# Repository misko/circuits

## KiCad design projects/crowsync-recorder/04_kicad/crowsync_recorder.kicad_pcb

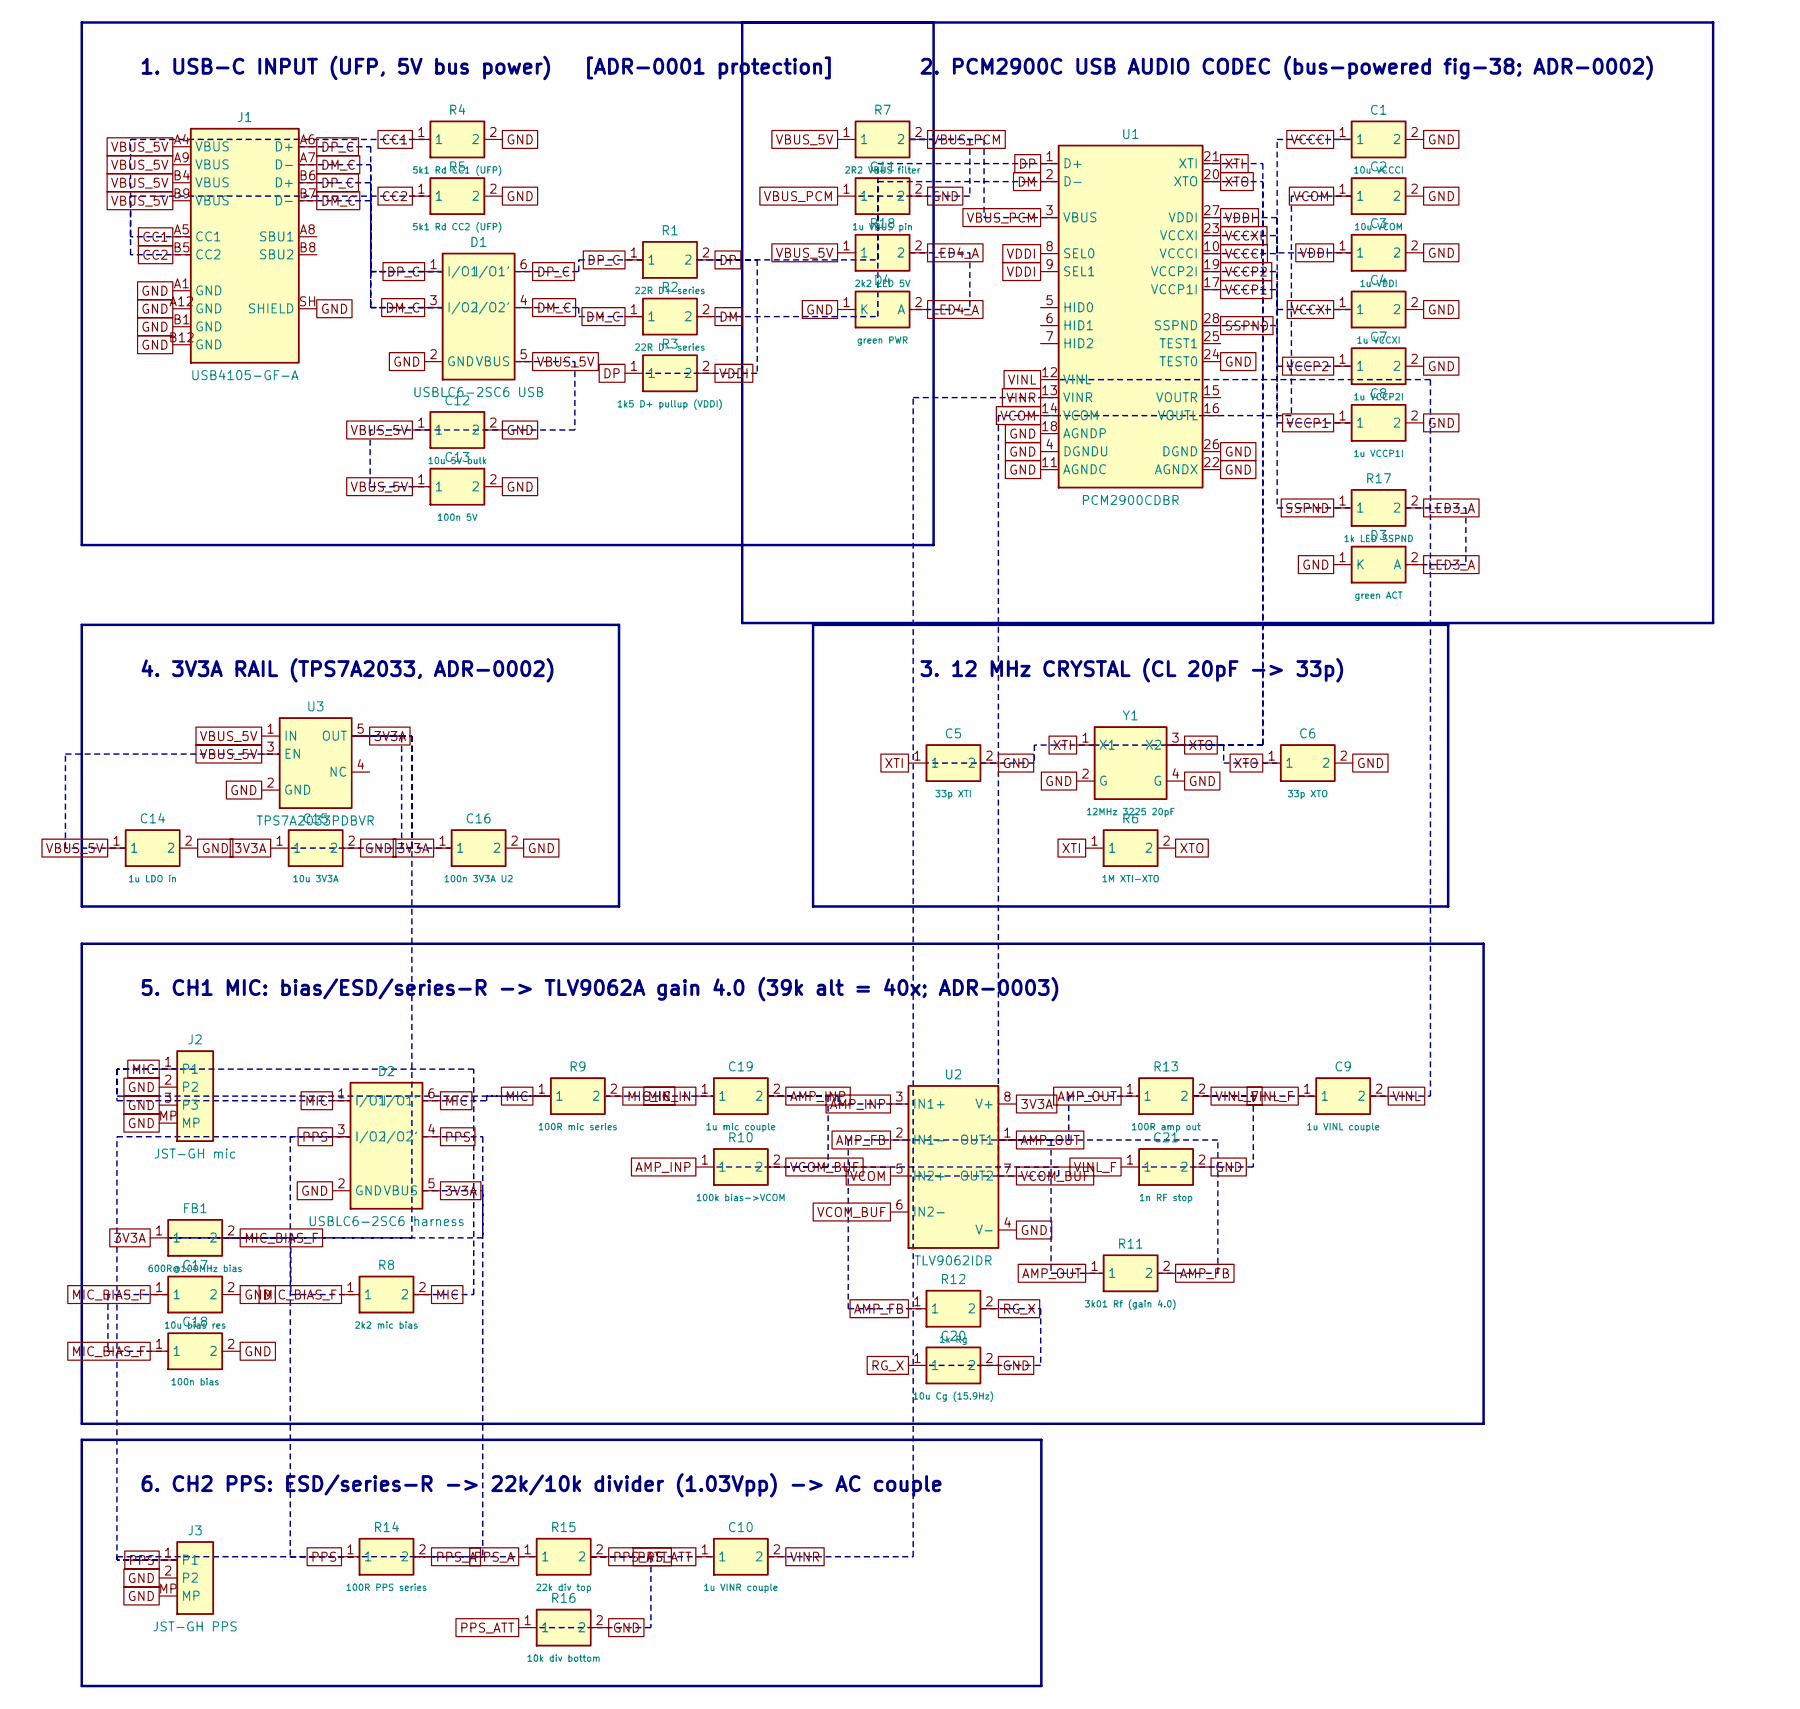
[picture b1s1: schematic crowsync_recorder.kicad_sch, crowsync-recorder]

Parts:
C1: 10u VCCCI; C_0603_1608Metric
C2: 10u VCOM; C_0603_1608Metric
C3: 1u VDDI; C_0603_1608Metric
C4: 1u VCCXI; C_0603_1608Metric
C5: 33p XTI; C_0603_1608Metric
C6: 33p XTO; C_0603_1608Metric
C7: 1u VCCP2I; C_0603_1608Metric
C8: 1u VCCP1I; C_0603_1608Metric
C9: 1u VINL couple; C_0603_1608Metric
C10: 1u VINR couple; C_0603_1608Metric
C11: 1u VBUS pin; C_0603_1608Metric
C12: 10u 5V bulk; C_0603_1608Metric
C13: 100n 5V; C_0603_1608Metric
C14: 1u LDO in; C_0603_1608Metric
C15: 10u 3V3A; C_0603_1608Metric
C16: 100n 3V3A U2; C_0603_1608Metric
C17: 10u bias res; C_0603_1608Metric
C18: 100n bias; C_0603_1608Metric
C19: 1u mic couple; C_0603_1608Metric
C20: 10u Cg (15.9Hz); C_0603_1608Metric
C21: 1n RF stop; C_0603_1608Metric
D1: USBLC6-2SC6 USB; SOT-23-6
D2: USBLC6-2SC6 harness; SOT-23-6
D3: green ACT; LED_0805_2012Metric
D4: green PWR; LED_0805_2012Metric
FB1: 600R@100MHz bias; L_0603_1608Metric
J1: USB4105-GF-A; USB_C_Receptacle_GCT_USB4105-xx-A_16P_TopMnt_Horizontal
J2: JST-GH mic; JST_GH_SM03B-GHS-TB_1x03-1MP_P1.25mm_Horizontal
J3: JST-GH PPS; JST_GH_SM02B-GHS-TB_1x02-1MP_P1.25mm_Horizontal
R1: 22R D+ series; R_0603_1608Metric
R2: 22R D- series; R_0603_1608Metric
R3: 1k5 D+ pullup (VDDI); R_0603_1608Metric
R4: 5k1 Rd CC1 (UFP); R_0603_1608Metric
R5: 5k1 Rd CC2 (UFP); R_0603_1608Metric
R6: 1M XTI-XTO; R_0603_1608Metric
R7: 2R2 VBUS filter; R_0603_1608Metric
R8: 2k2 mic bias; R_0603_1608Metric
R9: 100R mic series; R_0603_1608Metric
R10: 100k bias->VCOM; R_0603_1608Metric
R11: 3k01 Rf (gain 4.0); R_0603_1608Metric
R12: 1k Rg; R_0603_1608Metric
R13: 100R amp out; R_0603_1608Metric
R14: 100R PPS series; R_0603_1608Metric
R15: 22k div top; R_0603_1608Metric
R16: 10k div bottom; R_0603_1608Metric
R17: 1k LED SSPND; R_0603_1608Metric
R18: 2k2 LED 5V; R_0603_1608Metric
U1: PCM2900CDBR; SSOP-28_5.3x10.2mm_P0.65mm
U2: TLV9062IDR; SOIC-8_3.9x4.9mm_P1.27mm
U3: TPS7A2033PDBVR; SOT-23-5
Y1: 12MHz 3225 20pF; Crystal_SMD_3225-4Pin_3.2x2.5mm

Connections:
3V3A: C15.1, C16.1, D2.5 (VBUS), FB1.1, U2.8 (V+), U3.5 (OUT)
AMP_FB: R11.2, R12.1, U2.2 (IN1-)
AMP_INP: C19.2, R10.1, U2.3 (IN1+)
AMP_OUT: R11.1, R13.1, U2.1 (OUT1)
CC1: J1.A5 (CC1), R4.1
CC2: J1.B5 (CC2), R5.1
DM: R2.2, U1.2 (D-)
DM_C: D1.3 (I/O2), D1.4 (I/O2'), J1.A7 (D-), J1.B7 (D-), R2.1
DP: R1.2, R3.1, U1.1 (D+)
DP_C: D1.1 (I/O1), D1.6 (I/O1'), J1.A6 (D+), J1.B6 (D+), R1.1
GND: C1.2, C2.2, C3.2, C4.2, C5.2, C6.2, C7.2, C8.2, C11.2, C12.2, C13.2, C14.2, C15.2, C16.2, C17.2, C18.2, C20.2, C21.2, D1.2 (GND), D2.2 (GND), D3.1 (K), D4.1 (K), J1.A1 (GND), J1.A12 (GND), J1.B1 (GND), J1.B12 (GND), J1.SH (SHIELD), J2.2, J2.3, J2.MP, J3.2, J3.MP, R4.2, R5.2, R16.2, U1.4 (DGNDU), U1.11 (AGNDC), U1.18 (AGNDP), U1.22 (AGNDX), U1.24 (TEST0), U1.26 (DGND), U2.4 (V-), U3.2 (GND), Y1.2 (G), Y1.4 (G)
LED3_A: D3.2 (A), R17.2
LED4_A: D4.2 (A), R18.2
MIC: D2.1 (I/O1), D2.6 (I/O1'), J2.1, R8.2, R9.1
MIC_BIAS_F: C17.1, C18.1, FB1.2, R8.1
MIC_IN: C19.1, R9.2
PPS: D2.3 (I/O2), D2.4 (I/O2'), J3.1, R14.1
PPS_A: R14.2, R15.1
PPS_ATT: C10.1, R15.2, R16.1
RG_X: C20.1, R12.2
SSPND: R17.1, U1.28 (SSPND)
VBUS_5V: C12.1, C13.1, C14.1, D1.5 (VBUS), J1.A4 (VBUS), J1.A9 (VBUS), J1.B4 (VBUS), J1.B9 (VBUS), R7.1, R18.1, U3.1 (IN), U3.3 (EN)
VBUS_PCM: C11.1, R7.2, U1.3 (VBUS)
VCCCI: C1.1, U1.10 (VCCCI)
VCCP1: C8.1, U1.17 (VCCP1I)
VCCP2: C7.1, U1.19 (VCCP2I)
VCCXI: C4.1, U1.23 (VCCXI)
VCOM: C2.1, U1.14 (VCOM), U2.5 (IN2+)
VCOM_BUF: R10.2, U2.6 (IN2-), U2.7 (OUT2)
VDDI: C3.1, R3.2, U1.8 (SEL0), U1.9 (SEL1), U1.27 (VDDI)
VINL: C9.2, U1.12 (VINL)
VINL_F: C9.1, C21.1, R13.2
VINR: C10.2, U1.13 (VINR)
XTI: C5.1, R6.1, U1.21 (XTI), Y1.1 (X1)
XTO: C6.1, R6.2, U1.20 (XTO), Y1.3 (X2)

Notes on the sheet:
1. USB-C INPUT (UFP, 5V bus power) [ADR-0001 protection]
2. PCM2900C USB AUDIO CODEC (bus-powered fig-38; ADR-0002)
3. 12 MHz CRYSTAL (CL 20pF -> 33p)
4. 3V3A RAIL (TPS7A2033, ADR-0002)
5. CH1 MIC: bias/ESD/series-R -> TLV9062A gain 4.0 (39k alt = 40x; ADR-0003)
6. CH2 PPS: ESD/series-R -> 22k/10k divider (1.03Vpp) -> AC couple

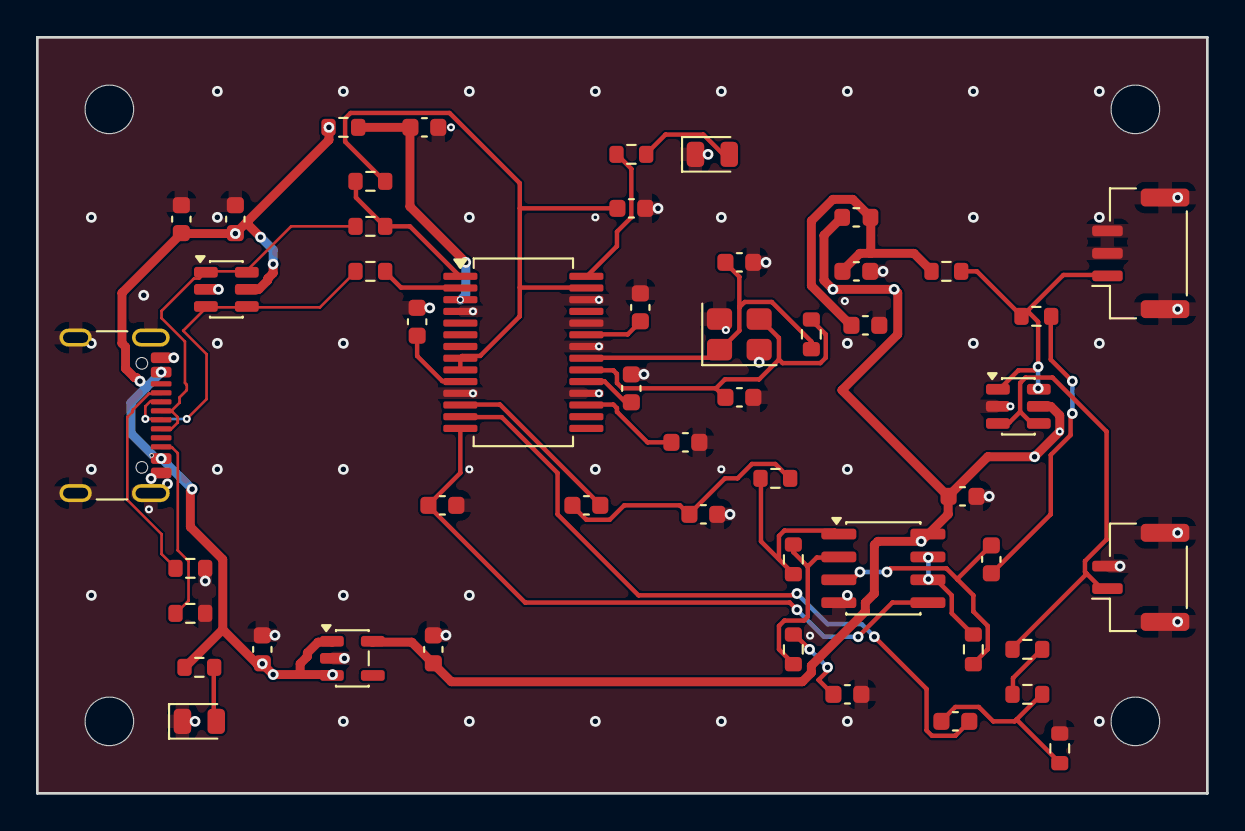
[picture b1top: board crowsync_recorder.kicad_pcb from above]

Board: 4 copper layers, 65.0 x 42.0 mm, 55 parts (0 on the bottom side), 35 nets.

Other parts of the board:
H1, H2, H3, H4: MountingHole_2.7mm_M2.5

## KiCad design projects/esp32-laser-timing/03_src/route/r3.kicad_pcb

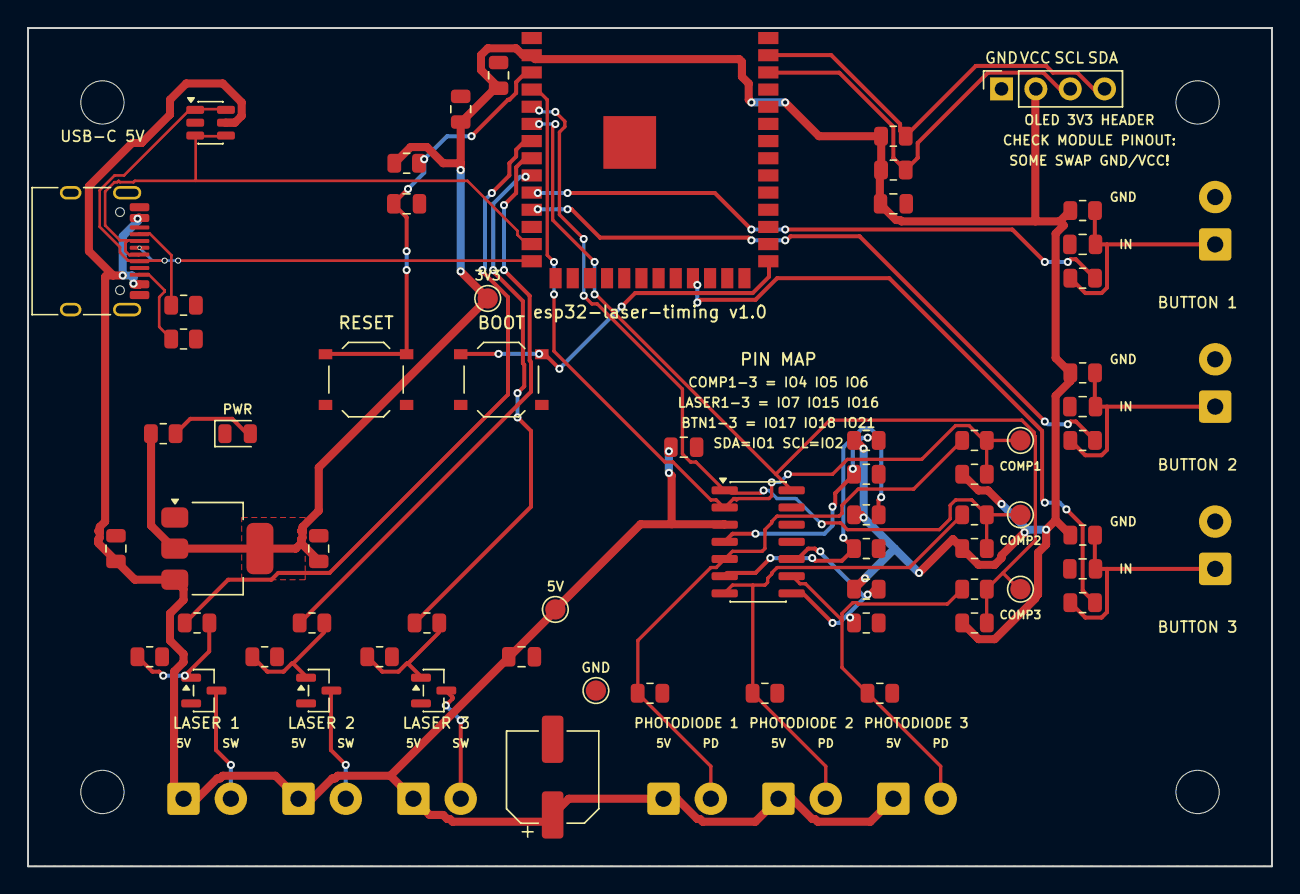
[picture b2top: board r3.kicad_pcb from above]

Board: 2 copper layers, 92.0 x 62.0 mm, 76 parts (0 on the bottom side), 36 nets.

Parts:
C1: 1u EN; C_0805_2012Metric
C2: 22u LDO in; C_0805_2012Metric
C3: 22u LDO out; C_0805_2012Metric
C4: 22u MCU 3V3; C_0805_2012Metric
C5: 100n MCU 3V3; C_0805_2012Metric
C6: 100n LM339; C_0805_2012Metric
C7: 100n OLED; C_0805_2012Metric
C8, C9, C10: 100n btn; C_0805_2012Metric
C11: 100u 5V bulk; CP_Elec_6.3x5.4
C12: 100n 5V bulk; C_0805_2012Metric
D1: USBLC6-2SC6; SOT-23-6
D2: green PWR; LED_0805_2012Metric
H1, H2, H3, H4: MountingHole_3.2mm_M3
J1: TYPE-C-31-M-12; USB_C_Receptacle_HRO_TYPE-C-31-M-12
J2: OLED HDR 1x4F; PinSocket_1x04_P2.54mm_Vertical
J4: LASER 1 TERM; TerminalBlock_3.5-2P_NoSilk
J5: LASER 2 TERM; TerminalBlock_3.5-2P_NoSilk
J6: LASER 3 TERM; TerminalBlock_3.5-2P_NoSilk
J7: PHOTODIODE 1 TERM; TerminalBlock_3.5-2P_NoSilk
J8: PHOTODIODE 2 TERM; TerminalBlock_3.5-2P_NoSilk
J9: PHOTODIODE 3 TERM; TerminalBlock_3.5-2P_NoSilk
J10: BUTTON 1 TERM; TerminalBlock_3.5-2P_NoSilk
J11: BUTTON 2 TERM; TerminalBlock_3.5-2P_NoSilk
J12: BUTTON 3 TERM; TerminalBlock_3.5-2P_NoSilk
Q1, Q2, Q3: AO3400A; SOT-23
R1: 5.1k CC1; R_0805_2012Metric
R2: 5.1k CC2; R_0805_2012Metric
R3: 10k EN; R_0805_2012Metric
R4: 1k LED; R_0805_2012Metric
R10, R12, R14: 100R gate; R_0805_2012Metric
R11, R13, R15: 100k gate pd; R_0805_2012Metric
R20, R21, R22: 1k PD load; R_0805_2012Metric
R23, R24, R25: 10k div top; R_0805_2012Metric
R26, R27, R28: 2.7k div bot; R_0805_2012Metric
R29, R30, R31: 33k hyst; R_0805_2012Metric
R32, R33, R34: 10k comp pu; R_0805_2012Metric
R40, R41, R42: 10k btn pu; R_0805_2012Metric
R43, R44, R45: 1k btn ser; R_0805_2012Metric
R50: 4.7k SDA pu; R_0805_2012Metric
R51: 4.7k SCL pu; R_0805_2012Metric
SW1: TS-1187A BOOT; SW_Push_1P1T_XKB_TS-1187A
SW2: TS-1187A RESET; SW_Push_1P1T_XKB_TS-1187A
TP1: TP COMP1; TestPoint_Pad_D1.5mm
TP2: TP COMP2; TestPoint_Pad_D1.5mm
TP3: TP COMP3; TestPoint_Pad_D1.5mm
TP4: TP 5V; TestPoint_Pad_D1.5mm
TP5: TP 3V3; TestPoint_Pad_D1.5mm
TP6: TP GND; TestPoint_Pad_D1.5mm
U1: ESP32-S3-WROOM-1-N8R2; ESP32-S3-WROOM-1
U2: AMS1117-3.3; SOT-223-3_TabPin2
U3: LM339DT; SOIC-14_3.9x8.7mm_P1.27mm

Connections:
3V3: C3.1, C4.1, C5.1, C7.1, J2.2, R3.1, R4.1, R23.1, R24.1, R25.1, R32.1, R33.1, R34.1, R40.1, R41.1, R42.1, R50.1, R51.1, TP5.1, U1.2, U2.2
5V: C2.1, C6.1, C11.1, C12.1, D1.5, J1.A4, J1.A9, J1.B4, J1.B9, J4.1, J5.1, J6.1, J7.1, J8.1, J9.1, TP4.1, U2.3, U3.3
BOOT: SW1.1, U1.27
BTN1_G: R43.2, U1.10
BTN1_N: C8.1, J10.1, R40.2, R43.1
BTN2_G: R44.2, U1.11
BTN2_N: C9.1, J11.1, R41.2, R44.1
BTN3_G: R45.2, U1.23
BTN3_N: C10.1, J12.1, R42.2, R45.1
CC1: J1.A5, R1.1
CC2: J1.B5, R2.1
COMP1: R29.2, R32.2, TP1.1, U1.4, U3.2
COMP2: R30.2, R33.2, TP2.1, U1.5, U3.1
COMP3: R31.2, R34.2, TP3.1, U1.6, U3.14
EN: C1.1, R3.2, SW2.1, U1.3
GATE1: Q1.1, R10.2, R11.1
GATE2: Q2.1, R12.2, R13.1
GATE3: Q3.1, R14.2, R15.1
GND: C1.2, C2.2, C3.2, C4.2, C5.2, C6.2, C7.2, C8.2, C9.2, C10.2, C11.2, C12.2, D1.2, D2.1, J1.A1, J1.A12, J1.B1, J1.B12, J1.SH, J2.1, J10.2, J11.2, J12.2, Q1.2, Q2.2, Q3.2, R1.2, R2.2, R11.2, R13.2, R15.2, R20.2, R21.2, R22.2, R26.2, R27.2, R28.2, SW1.2, SW2.2, TP6.1, U1.1, U1.40, U1.41, U2.1, U3.11, U3.12
LDRV1: R10.1, U1.7
LDRV2: R12.1, U1.8
LDRV3: R14.1, U1.9
LED_A: D2.2, R4.2
LSW1: J4.2, Q1.3
LSW2: J5.2, Q2.3
LSW3: J6.2, Q3.3
PD1: J7.2, R20.1, R29.1, U3.5
PD2: J8.2, R21.1, R30.1, U3.7
PD3: J9.2, R22.1, R31.1, U3.9
SCL: J2.3, R51.2, U1.38
SDA: J2.4, R50.2, U1.39
USB_DM: D1.3, D1.4, J1.A7, J1.B7, U1.13
USB_DP: D1.1, D1.6, J1.A6, J1.B6, U1.14
VTH1: R23.2, R26.1, U3.4
VTH2: R24.2, R27.1, U3.6
VTH3: R25.2, R28.1, U3.8, U3.10

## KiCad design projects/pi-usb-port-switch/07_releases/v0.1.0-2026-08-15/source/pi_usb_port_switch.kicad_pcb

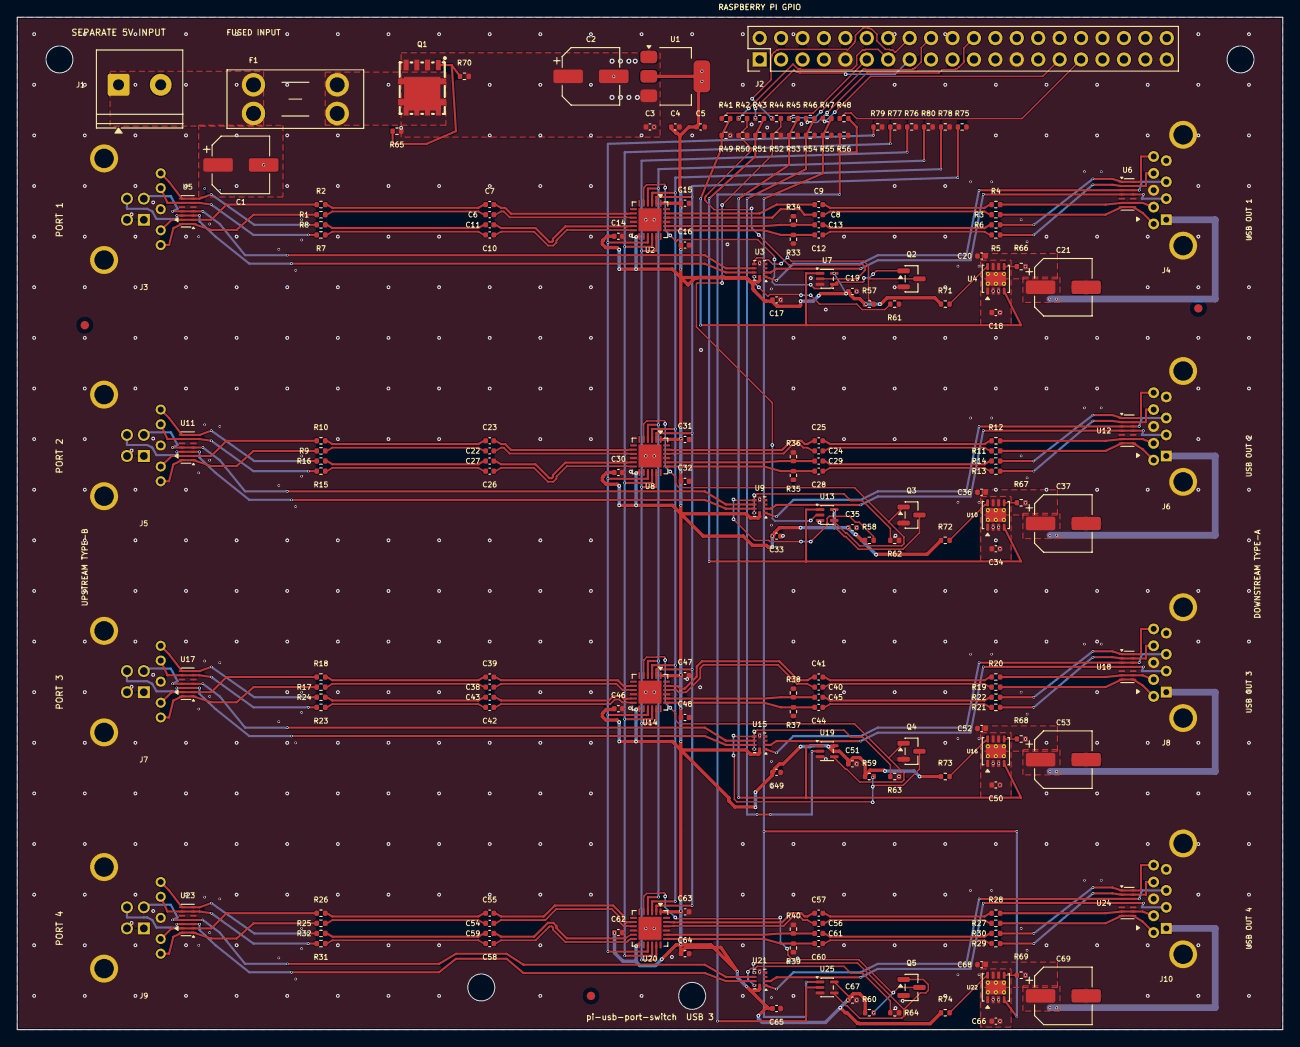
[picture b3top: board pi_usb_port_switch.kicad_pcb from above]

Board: 4 copper layers, 150.0 x 120.0 mm, 197 parts (0 on the bottom side), 164 nets.

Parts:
C1, C2: 180uF; CP_Elec_6.3x5.8
C3, C6, C7, C8, C9, C10, C11, C14, C15, C17, C18, C19, C20, C22, C23, C24, C25, C26, C27, C30, C31, C33, C34, C35, C36, C38, C39, C40, C41, C42, C43, C46, C47, C49, C50, C51, C52, C54, C55, C56, C57, C58, C59, C62, C63, C65, C66, C67, C68: 100nF; C_0402_1005Metric
C4: 1uF; C_0402_1005Metric
C5, C16, C32, C48, C64: 10uF; C_0402_1005Metric
C12, C13, C28, C29, C44, C45, C60, C61: 330nF; C_0402_1005Metric
C21, C37, C53, C69: 150uF; CP_Elec_6.3x5.8
F1: C5249699; Keystone_3568_Mini_Blade_Fuse_Holder
FID1, FID2, FID3: Fiducial_1mm_Mask2mm
H1, H2, H3, H4: MountingHole_3.2mm_M3
J1: C3819953; Phoenix_1935161_PT_1p5_2_5p0_H
J2: C5364405; PinHeader_2x20_P2.54mm_Vertical
J3, J5, J7, J9: C5334230; Wurth_692221030100_USB3_B
J4, J6, J8, J10: 692121030100; Wurth_692121030100_USB3_A
Q1: C397981; PowerDI5060-8
Q2, Q3, Q4, Q5: C85049; SOT-23
R1, R2, R3, R4, R5, R6, R7, R8, R9, R10, R11, R12, R13, R14, R15, R16, R17, R18, R19, R20, R21, R22, R23, R24, R25, R26, R27, R28, R29, R30, R31, R32: 2.2Ω; R_0402_1005Metric
R33, R34, R35, R36, R37, R38, R39, R40: 220kΩ; R_0402_1005Metric
R41, R42, R43, R44, R45, R46, R47, R48: 1kΩ; R_0402_1005Metric
R49, R50, R51, R52, R53, R54, R55, R56, R57, R58, R59, R60, R61, R62, R63, R64, R65, R66, R67, R68, R69: 100kΩ; R_0402_1005Metric
R70: 1MΩ; R_0402_1005Metric
R71, R72, R73, R74: 10kΩ; R_0402_1005Metric
R75, R76, R77, R78, R79, R80: 4.7kΩ; R_0402_1005Metric
U1: C7527500; SOT-223-3_TabPin2
U2, U8, U14, U20: C2675181; TUSB522P_RGE24_4x4_P0.5
U3, U9, U15, U21: C129313; TS3USB221E_RSE10_2x1.5_P0.4
U4, U10, U16, U22: C130056; VSON-8-1EP_3x3mm_P0.65mm_EP1.65x2.4mm_ThermalVias
U5, U6, U11, U12, U17, U18, U23, U24: C962978; TPD6E05U06_RVZ14_3.5x1.35_P0.5
U7, U13, U19, U25: C7832; SC-70-5

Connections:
3V3: C4.1, C5.1, C14.1, C15.1, C16.1, C17.1, C19.1, C30.1, C31.1, C32.1, C33.1, C35.1, C46.1, C47.1, C48.1, C49.1, C51.1, C62.1, C63.1, C64.1, C65.1, C67.1, R57.1, R58.1, R59.1, R60.1, R71.1, R72.1, R73.1, R74.1, U1.2, U2.1, U2.13, U3.10, U7.5, U8.1, U8.13, U9.10, U13.5, U14.1, U14.13, U15.10, U19.5, U20.1, U20.13, U21.10, U25.5
DATA_EN1: R42.2, R50.1, U7.2
DATA_EN2: R44.2, R52.1, U13.2
DATA_EN3: R46.2, R54.1, U19.2
DATA_EN4: R48.2, R56.1, U25.2
DATA_OK1: Q2.1, U2.5, U7.4
DATA_OK2: Q3.1, U8.5, U13.4
DATA_OK3: Q4.1, U14.5, U19.4
DATA_OK4: Q5.1, U20.5, U25.4
EXT_5V_FUSED: F1.2, Q1.5, Q1.6, Q1.7, Q1.8
EXT_5V_RAW: C1.1, F1.1, J1.1
GND: C1.2, C2.2, C3.2, C4.2, C5.2, C14.2, C15.2, C16.2, C17.2, C18.2, C19.2, C20.2, C21.2, C30.2, C31.2, C32.2, C33.2, C34.2, C35.2, C36.2, C37.2, C46.2, C47.2, C48.2, C49.2, C50.2, C51.2, C52.2, C53.2, C62.2, C63.2, C64.2, C65.2, C66.2, C67.2, C68.2, C69.2, J1.2, J2.6, J2.9, J2.14, J2.20, J2.25, J2.30, J2.34, J2.39, J3.4, J3.7, J3.10, J4.4, J4.7, J4.10, J5.4, J5.7, J5.10, J6.4, J6.7, J6.10, J7.4, J7.7, J7.10, J8.4, J8.7, J8.10, J9.4, J9.7, J9.10, J10.4, J10.7, J10.10, Q2.2, Q3.2, Q4.2, Q5.2, R33.2, R34.2, R35.2, R36.2, R37.2, R38.2, R39.2, R40.2, R49.2, R50.2, R51.2, R52.2, R53.2, R54.2, R55.2, R56.2, R61.2, R62.2, R63.2, R64.2, R65.2, R66.2, R67.2, R68.2, R69.2, R75.2, R76.2, R77.2, R78.2, R79.2, R80.2, U1.1, U2.10, U2.21, U2.25, U3.5, U4.1, U4.9, U5.5, U5.10, U6.5, U6.10, U7.3, U8.10, U8.21, U8.25, U9.5, U10.1, U10.9, U11.5, U11.10, U12.5, U12.10, U13.3, U14.10, U14.21, U14.25, U15.5, U16.1, U16.9, U17.5, U17.10, U18.5, U18.10, U19.3, U20.10, U20.21, U20.25, U21.5, U22.1, U22.9, U23.5, U23.10, U24.5, U24.10, U25.3
GPIO5_RAW: J2.29, R47.1
GPIO6_RAW: J2.31, R48.1
GPIO17_RAW: J2.11, R41.1
GPIO22_RAW: J2.15, R43.1
GPIO23_RAW: J2.16, R44.1
GPIO24_RAW: J2.18, R45.1
GPIO25_RAW: J2.22, R46.1
GPIO27_RAW: J2.13, R42.1
ILIM1: R66.1, U4.5
ILIM2: R67.1, U10.5
ILIM3: R68.1, U16.5
ILIM4: R69.1, U22.5
P5V_PROTECTED: C2.1, C3.1, C18.1, C34.1, C50.1, C66.1, Q1.2, Q1.3, Q1.4, R70.1, U1.3, U4.2, U4.3, U10.2, U10.3, U16.2, U16.3, U22.2, U22.3
PWR_EN1: R41.2, R49.1, U4.4, U7.1
PWR_EN2: R43.2, R51.1, U10.4, U13.1
PWR_EN3: R45.2, R53.1, U16.4, U19.1
PWR_EN4: R47.2, R55.1, U22.4, U25.1
RPP_GATE: Q1.1, R65.1, R70.2
TUSB_DE1: R77.1, U2.16, U8.16, U14.16, U20.16
TUSB_DE2: R78.1, U2.3, U8.3, U14.3, U20.3
TUSB_EQ1: R75.1, U2.2, U8.2, U14.2, U20.2
TUSB_EQ2: R76.1, U2.17, U8.17, U14.17, U20.17
TUSB_OS1: R79.1, U2.15, U8.15, U14.15, U20.15
TUSB_OS2: R80.1, U2.4, U8.4, U14.4, U20.4
USB1_HS_DN_N: J4.2, U3.2, U6.4, U6.11
USB1_HS_DN_P: J4.3, U3.1, U6.3, U6.12
USB1_HS_UP_N: J3.2, U3.7, U5.4, U5.11
USB1_HS_UP_P: J3.3, U3.8, U5.3, U5.12
USB1_SS_RX_DN_CONN_N: J4.5, R6.1, U6.1, U6.14
USB1_SS_RX_DN_CONN_P: J4.6, R5.1, U6.2, U6.13
USB1_SS_RX_DN_IC_N: C13.2, R34.1, U2.20
USB1_SS_RX_DN_IC_P: C12.2, R33.1, U2.19
USB1_SS_RX_DN_MID_N: C13.1, R6.2
USB1_SS_RX_DN_MID_P: C12.1, R5.2
USB1_SS_RX_UP_CONN_N: J3.5, R8.1, U5.7, U5.8
USB1_SS_RX_UP_CONN_P: J3.6, R7.1, U5.6, U5.9
USB1_SS_RX_UP_IC_N: C11.1, U2.11
USB1_SS_RX_UP_IC_P: C10.1, U2.12
USB1_SS_RX_UP_MID_N: C11.2, R8.2
USB1_SS_RX_UP_MID_P: C10.2, R7.2
USB1_SS_TX_DN_CONN_N: J4.8, R4.1, U6.6, U6.9
USB1_SS_TX_DN_CONN_P: J4.9, R3.1, U6.7, U6.8
USB1_SS_TX_DN_IC_N: C9.1, U2.23
USB1_SS_TX_DN_IC_P: C8.1, U2.22
USB1_SS_TX_DN_MID_N: C9.2, R4.2
USB1_SS_TX_DN_MID_P: C8.2, R3.2
USB1_SS_TX_UP_CONN_N: J3.8, R2.1, U5.2, U5.13
USB1_SS_TX_UP_CONN_P: J3.9, R1.1, U5.1, U5.14
USB1_SS_TX_UP_IC_N: C7.2, U2.8
USB1_SS_TX_UP_IC_P: C6.2, U2.9
USB1_SS_TX_UP_MID_N: C7.1, R2.2
USB1_SS_TX_UP_MID_P: C6.1, R1.2
USB2_HS_DN_N: J6.2, U9.2, U12.4, U12.11
USB2_HS_DN_P: J6.3, U9.1, U12.3, U12.12
USB2_HS_UP_N: J5.2, U9.7, U11.4, U11.11
USB2_HS_UP_P: J5.3, U9.8, U11.3, U11.12
USB2_OE1: Q2.3, R57.2, U3.6
USB2_OE2: Q3.3, R58.2, U9.6
USB2_OE3: Q4.3, R59.2, U15.6
USB2_OE4: Q5.3, R60.2, U21.6
USB2_SEL1: R61.1, U3.9
USB2_SEL2: R62.1, U9.9
USB2_SEL3: R63.1, U15.9
USB2_SEL4: R64.1, U21.9
USB2_SS_RX_DN_CONN_N: J6.5, R14.1, U12.1, U12.14
USB2_SS_RX_DN_CONN_P: J6.6, R13.1, U12.2, U12.13
USB2_SS_RX_DN_IC_N: C29.2, R36.1, U8.20
USB2_SS_RX_DN_IC_P: C28.2, R35.1, U8.19
USB2_SS_RX_DN_MID_N: C29.1, R14.2
USB2_SS_RX_DN_MID_P: C28.1, R13.2
USB2_SS_RX_UP_CONN_N: J5.5, R16.1, U11.7, U11.8
USB2_SS_RX_UP_CONN_P: J5.6, R15.1, U11.6, U11.9
USB2_SS_RX_UP_IC_N: C27.1, U8.11
USB2_SS_RX_UP_IC_P: C26.1, U8.12
USB2_SS_RX_UP_MID_N: C27.2, R16.2
USB2_SS_RX_UP_MID_P: C26.2, R15.2
USB2_SS_TX_DN_CONN_N: J6.8, R12.1, U12.6, U12.9
USB2_SS_TX_DN_CONN_P: J6.9, R11.1, U12.7, U12.8
USB2_SS_TX_DN_IC_N: C25.1, U8.23
USB2_SS_TX_DN_IC_P: C24.1, U8.22
USB2_SS_TX_DN_MID_N: C25.2, R12.2
USB2_SS_TX_DN_MID_P: C24.2, R11.2
USB2_SS_TX_UP_CONN_N: J5.8, R10.1, U11.2, U11.13
USB2_SS_TX_UP_CONN_P: J5.9, R9.1, U11.1, U11.14
USB2_SS_TX_UP_IC_N: C23.2, U8.8
USB2_SS_TX_UP_IC_P: C22.2, U8.9
USB2_SS_TX_UP_MID_N: C23.1, R10.2
USB2_SS_TX_UP_MID_P: C22.1, R9.2
USB3_HS_DN_N: J8.2, U15.2, U18.4, U18.11
USB3_HS_DN_P: J8.3, U15.1, U18.3, U18.12
USB3_HS_UP_N: J7.2, U15.7, U17.4, U17.11
USB3_HS_UP_P: J7.3, U15.8, U17.3, U17.12
USB3_SS_RX_DN_CONN_N: J8.5, R22.1, U18.1, U18.14
USB3_SS_RX_DN_CONN_P: J8.6, R21.1, U18.2, U18.13
USB3_SS_RX_DN_IC_N: C45.2, R38.1, U14.20
USB3_SS_RX_DN_IC_P: C44.2, R37.1, U14.19
USB3_SS_RX_DN_MID_N: C45.1, R22.2
USB3_SS_RX_DN_MID_P: C44.1, R21.2
USB3_SS_RX_UP_CONN_N: J7.5, R24.1, U17.7, U17.8
USB3_SS_RX_UP_CONN_P: J7.6, R23.1, U17.6, U17.9
USB3_SS_RX_UP_IC_N: C43.1, U14.11
USB3_SS_RX_UP_IC_P: C42.1, U14.12
USB3_SS_RX_UP_MID_N: C43.2, R24.2
USB3_SS_RX_UP_MID_P: C42.2, R23.2
USB3_SS_TX_DN_CONN_N: J8.8, R20.1, U18.6, U18.9
USB3_SS_TX_DN_CONN_P: J8.9, R19.1, U18.7, U18.8
USB3_SS_TX_DN_IC_N: C41.1, U14.23
USB3_SS_TX_DN_IC_P: C40.1, U14.22
USB3_SS_TX_DN_MID_N: C41.2, R20.2
USB3_SS_TX_DN_MID_P: C40.2, R19.2
USB3_SS_TX_UP_CONN_N: J7.8, R18.1, U17.2, U17.13
USB3_SS_TX_UP_CONN_P: J7.9, R17.1, U17.1, U17.14
USB3_SS_TX_UP_IC_N: C39.2, U14.8
USB3_SS_TX_UP_IC_P: C38.2, U14.9
USB3_SS_TX_UP_MID_N: C39.1, R18.2
USB3_SS_TX_UP_MID_P: C38.1, R17.2
USB4_HS_DN_N: J10.2, U21.2, U24.4, U24.11
USB4_HS_DN_P: J10.3, U21.1, U24.3, U24.12
USB4_HS_UP_N: J9.2, U21.7, U23.4, U23.11
USB4_HS_UP_P: J9.3, U21.8, U23.3, U23.12
USB4_SS_RX_DN_CONN_N: J10.5, R30.1, U24.1, U24.14
USB4_SS_RX_DN_CONN_P: J10.6, R29.1, U24.2, U24.13
USB4_SS_RX_DN_IC_N: C61.2, R40.1, U20.20
USB4_SS_RX_DN_IC_P: C60.2, R39.1, U20.19
USB4_SS_RX_DN_MID_N: C61.1, R30.2
USB4_SS_RX_DN_MID_P: C60.1, R29.2
USB4_SS_RX_UP_CONN_N: J9.5, R32.1, U23.7, U23.8
USB4_SS_RX_UP_CONN_P: J9.6, R31.1, U23.6, U23.9
USB4_SS_RX_UP_IC_N: C59.1, U20.11
USB4_SS_RX_UP_IC_P: C58.1, U20.12
USB4_SS_RX_UP_MID_N: C59.2, R32.2
USB4_SS_RX_UP_MID_P: C58.2, R31.2
USB4_SS_TX_DN_CONN_N: J10.8, R28.1, U24.6, U24.9
USB4_SS_TX_DN_CONN_P: J10.9, R27.1, U24.7, U24.8
USB4_SS_TX_DN_IC_N: C57.1, U20.23
USB4_SS_TX_DN_IC_P: C56.1, U20.22
USB4_SS_TX_DN_MID_N: C57.2, R28.2
USB4_SS_TX_DN_MID_P: C56.2, R27.2
USB4_SS_TX_UP_CONN_N: J9.8, R26.1, U23.2, U23.13
USB4_SS_TX_UP_CONN_P: J9.9, R25.1, U23.1, U23.14
USB4_SS_TX_UP_IC_N: C55.2, U20.8
USB4_SS_TX_UP_IC_P: C54.2, U20.9
USB4_SS_TX_UP_MID_N: C55.1, R26.2
USB4_SS_TX_UP_MID_P: C54.1, R25.2
VBUS1_SW: C20.1, C21.1, J4.1, U4.6, U4.7
VBUS2_SW: C36.1, C37.1, J6.1, U10.6, U10.7
VBUS3_SW: C52.1, C53.1, J8.1, U16.6, U16.7
VBUS4_SW: C68.1, C69.1, J10.1, U22.6, U22.7
VBUS_FAULT1_N: R71.2, U4.8
VBUS_FAULT2_N: R72.2, U10.8
VBUS_FAULT3_N: R73.2, U16.8
VBUS_FAULT4_N: R74.2, U22.8

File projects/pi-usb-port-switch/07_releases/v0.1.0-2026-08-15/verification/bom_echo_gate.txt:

F-ECHO — JLC's RESOLVED BOM vs OURS. After uploading bom.csv,
save JLC's own resolved/matched part table out of their UI and run
  bom_legibility_check.py <this outdir>/bom.csv --echo SAVED.csv
A code JLC redirects is a SUBSTITUTION and is a FINDING, not a
convenience. C82317 -> C131025 happened on a shipped board and no
gate in this repo could have seen it.

C60491	100kΩ	R49,R50,R51,R52,R53,R54,R55,R56,R57,R58,R59,R60,R61,R62,R63,R64,R65,R66,R67,R68,R69
C1525	100nF	C10,C11,C14,C15,C17,C18,C19,C20,C22,C23,C24,C25,C26,C27,C3,C30,C31,C33,C34,C35,C36,C38,C39,C40,C41,C42,C43,C46,C47,C49,C50,C51,C52,C54,C55,C56,C57,C58,C59,C6,C62,C63,C65,C66,C67,C68,C7,C8,C9
C60490	10kΩ	R71,R72,R73,R74
C15525	10uF	C16,C32,C48,C5,C64
C264054	150uF	C21,C37,C53,C69
C136277	180uF	C1,C2
C3819953	1935161	J1
C138033	1MΩ	R70
C106235	1kΩ	R41,R42,R43,R44,R45,R46,R47,R48
C52923	1uF	C4
C327251	2.2Ω	R1,R10,R11,R12,R13,R14,R15,R16,R17,R18,R19,R2,R20,R21,R22,R23,R24,R25,R26,R27,R28,R29,R3,R30,R31,R32,R4,R5,R6,R7,R8,R9
C138030	220kΩ	R33,R34,R35,R36,R37,R38,R39,R40
C85049	2N7002-7-F	Q2,Q3,Q4,Q5
C19271634	330nF	C12,C13,C28,C29,C44,C45,C60,C61
C5249699	3568	F1
C105871	4.7kΩ	R75,R76,R77,R78,R79,R80
C5364405	61304021121	J2
C5334230	692221030100	J3,J5,J7,J9
C397981	DMP3007SPS-13	Q1
C7832	SN74LVC1G08DCKR	U13,U19,U25,U7
C7527500	TLV76133DCYR	U1
C962978	TPD6E05U06RVZR	U11,U12,U17,U18,U23,U24,U5,U6
C130056	TPS2557DRBR	U10,U16,U22,U4
C129313	TS3USB221ERSER	U15,U21,U3,U9
C2675181	TUSB522PIRGER	U14,U2,U20,U8

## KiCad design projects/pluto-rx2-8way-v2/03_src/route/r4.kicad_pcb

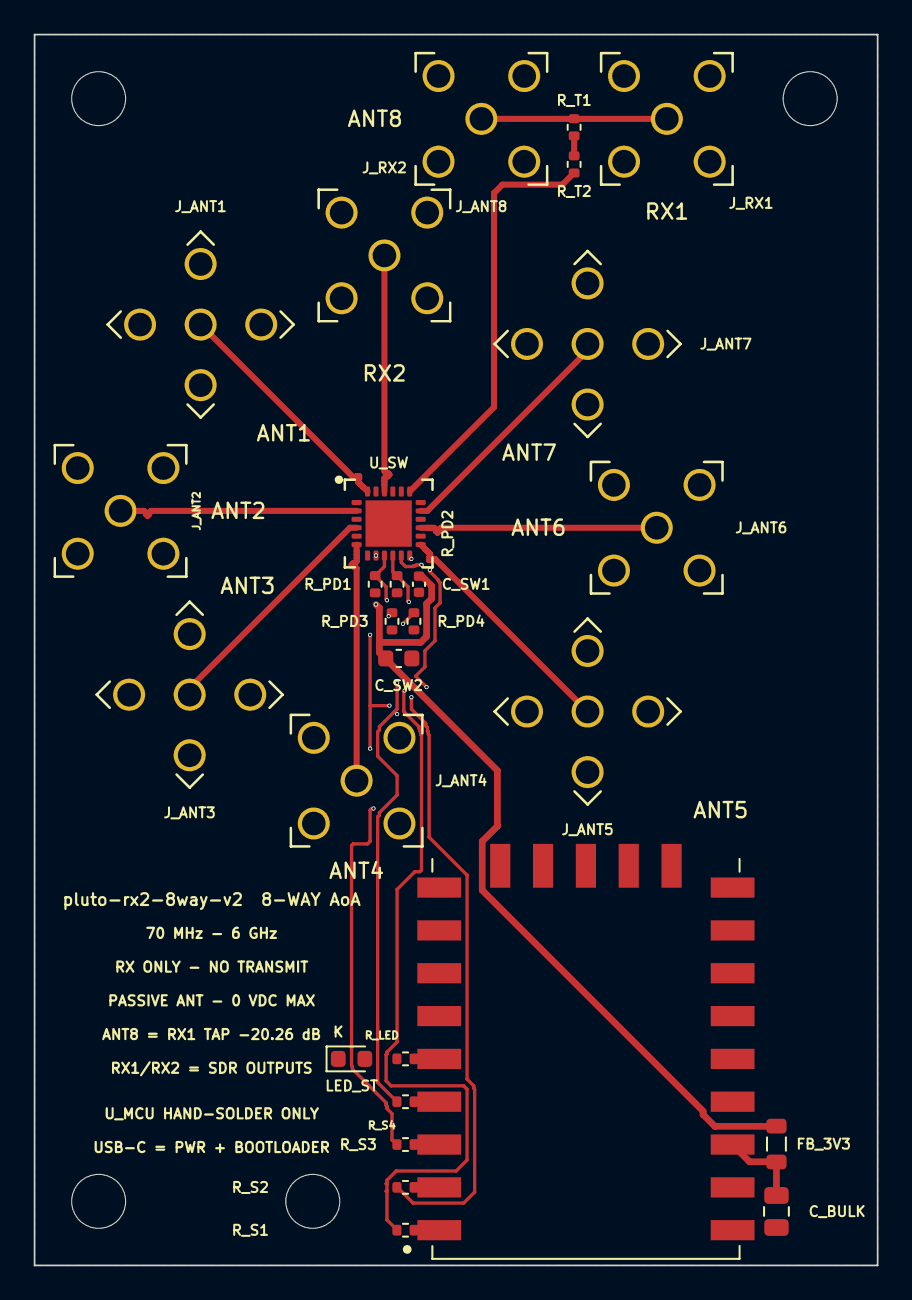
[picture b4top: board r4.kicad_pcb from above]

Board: 4 copper layers, 50.0 x 73.0 mm, 32 parts (0 on the bottom side), 24 nets.

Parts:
C_BULK: 4.7uF; C_0805_2012Metric
C_SW1: 100nF; C_0402_1005Metric
C_SW2: 1uF; C_0603_1608Metric
FB_3V3: C3716677; L_0805_2012Metric
H1, H2, H3, H4: MountingHole_3.2mm_M3
J_ANT1, J_ANT2, J_ANT3, J_ANT4, J_ANT5, J_ANT6, J_ANT7, J_ANT8: C504007; SMA_Vertical_5.08sq_D1.4
J_RX1, J_RX2: C504007; SMA_Vertical_5.08sq_D1.4
LED_ST: C2286; LED_0603_1608Metric
R_LED: 680Ω; R_0402_1005Metric
R_PD1, R_PD2, R_PD3, R_PD4: 10kΩ; R_0402_1005Metric
R_S1, R_S2, R_S3, R_S4: 47Ω; R_0402_1005Metric
R_T1, R_T2: 220Ω; R_0402_1005Metric
U_MCU: C9900173620; RP2040_Zero_LCC23_18x23.5
U_SW: C5121458; QFN-24_4x4_P0.5_EP2.7_PE42482

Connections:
3V3: C_SW1.1, C_SW2.1, FB_3V3.2, U_SW.8
3V3_MOD: C_BULK.1, FB_3V3.1, U_MCU.21
ANT1: J_ANT1.1, U_SW.24
ANT2: J_ANT2.1, U_SW.2
ANT3: J_ANT3.1, U_SW.4
ANT4: J_ANT4.1, U_SW.6
ANT5: J_ANT5.1, U_SW.13
ANT6: J_ANT6.1, U_SW.15
ANT7: J_ANT7.1, U_SW.17
GND: C_BULK.2, C_SW1.2, C_SW2.2, J_ANT1.2, J_ANT1.3, J_ANT1.4, J_ANT1.5, J_ANT2.2, J_ANT2.3, J_ANT2.4, J_ANT2.5, J_ANT3.2, J_ANT3.3, J_ANT3.4, J_ANT3.5, J_ANT4.2, J_ANT4.3, J_ANT4.4, J_ANT4.5, J_ANT5.2, J_ANT5.3, J_ANT5.4, J_ANT5.5, J_ANT6.2, J_ANT6.3, J_ANT6.4, J_ANT6.5, J_ANT7.2, J_ANT7.3, J_ANT7.4, J_ANT7.5, J_ANT8.2, J_ANT8.3, J_ANT8.4, J_ANT8.5, J_RX1.2, J_RX1.3, J_RX1.4, J_RX1.5, J_RX2.2, J_RX2.3, J_RX2.4, J_RX2.5, LED_ST.1, R_PD1.2, R_PD2.2, R_PD3.2, R_PD4.2, U_MCU.22, U_SW.1, U_SW.3, U_SW.5, U_SW.7, U_SW.14, U_SW.16, U_SW.18, U_SW.20, U_SW.21, U_SW.23, U_SW.25
LED_STAT: R_LED.1, U_MCU.5
LED_STAT_A: LED_ST.2, R_LED.2
RX1_MAIN: J_ANT8.1, J_RX1.1, R_T1.1
RX1_TAP: R_T2.2, U_SW.19
RX1_TAP_MID: R_T1.2, R_T2.1
RX2_OUT: J_RX2.1, U_SW.22
SEL_V1: R_S1.1, U_MCU.1
SEL_V2: R_S2.1, U_MCU.2
SEL_V3: R_S3.1, U_MCU.3
SEL_V4: R_S4.1, U_MCU.4
SW_V1: R_PD1.1, R_S1.2, U_SW.9
SW_V2: R_PD2.1, R_S2.2, U_SW.10
SW_V3: R_PD3.1, R_S3.2, U_SW.11
SW_V4: R_PD4.1, R_S4.2, U_SW.12
